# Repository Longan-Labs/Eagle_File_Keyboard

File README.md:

More details please goto [Longan Labs](https://longan-labs.cc/)

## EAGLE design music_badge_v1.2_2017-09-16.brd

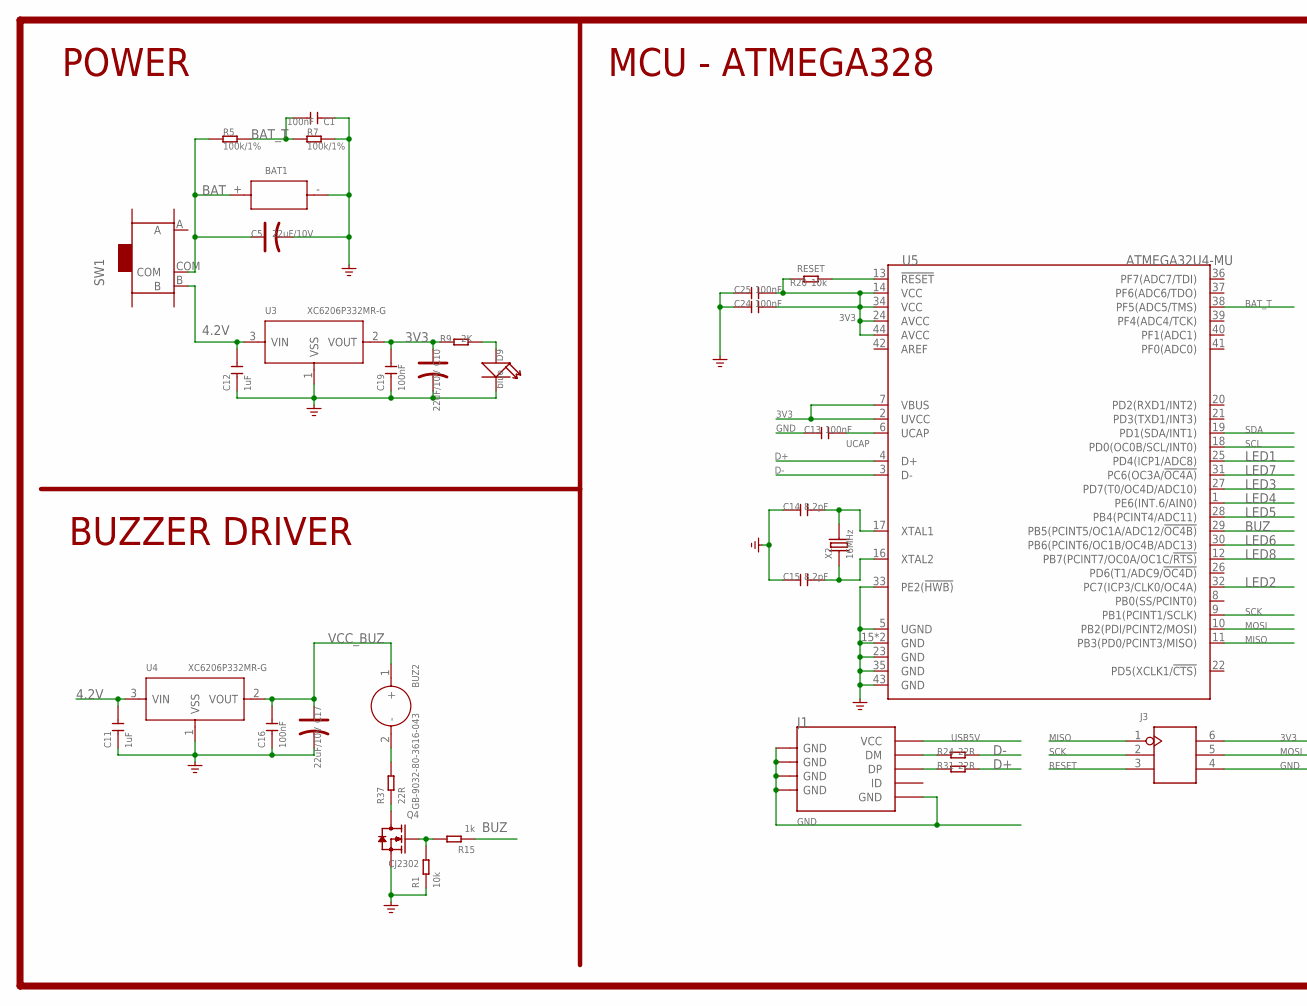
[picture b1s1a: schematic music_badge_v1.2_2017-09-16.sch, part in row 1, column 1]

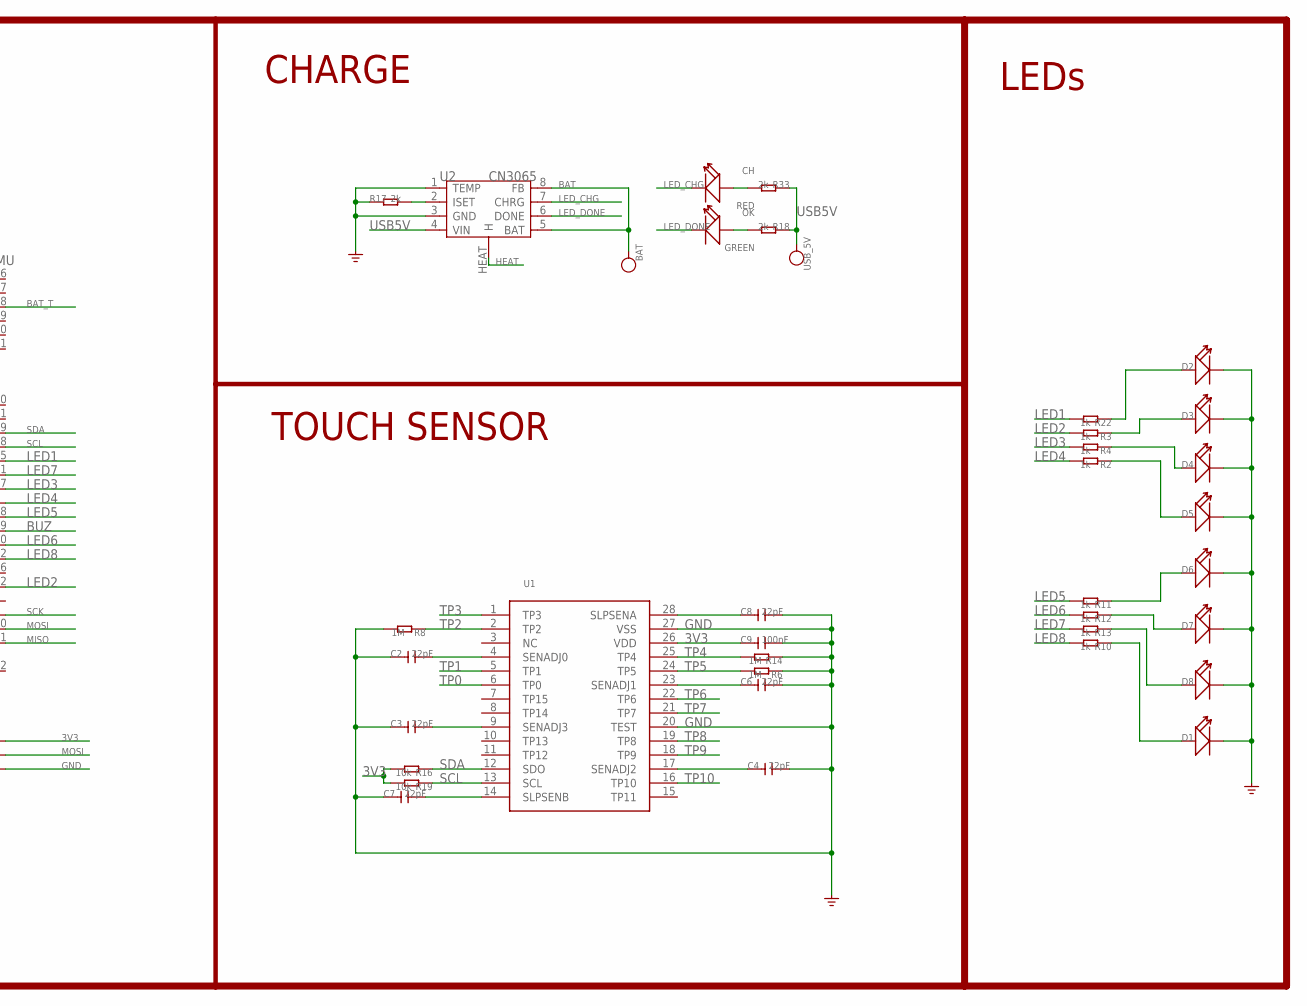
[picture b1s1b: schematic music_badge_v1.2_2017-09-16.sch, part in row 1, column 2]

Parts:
BAT: TEST-POINT-35; TP_3535
BAT1: HOLDER-BATTERY; 2P-SMD-L28.5*W16*H5.5
BUZ2: GB-9032-80-3616-043; BZ2-SMD-9X10.6X3.2MM
C1, C9, C13, C16, C19, C24, C25: 100nF; C0603
C2, C3, C4, C6, C7, C8: 22pF; C0603
C5, C10, C17: 22uF/10V; AVX-B
C11, C12: 1uF; C0603
C14, C15: 8.2pF; C0603
CH: RED; LED-0603
D1, D2, D3, D4, D5, D6, D7, D8: LED-3MM; LED-2P-2.54-3MM
D9: blue; LED-0603@1
J1: USB-MINIUSB-5P-MICRO; MICRO-USB
J3: HEADER-2X3P-2.0-1.143; H2X3-SMD-2.0(1.143)
OK: GREEN; LED-0603
Q4: CJ2302; SOT-23
R1, R16, R19, R20: 10k; R0603
R2, R3, R4, R10, R11, R12, R13, R15, R22: 1k; R0603
R5, R7: 100k/1%; R0603
R6, R8, R14: 1M; R0603
R9: 2K; R0603
R17, R18, R33: 2k; R0603
R24, R31, R37: 22R; R0603
SW1: SWITCH-3P-SMD-6.6X2.8; 3P-SMD-2CH-6.6X2.8-REINFORCE
U1: TTP229-BSF; SSOP28-0.635-10X4MM
U2: CN3065; DFN8
U3, U4: XC6206P332MR-G; SOT-23
U5: ATMEGA32U4-MU; QFN44
USB_5V: TEST-POINT-35; TP_3535
X2: 16MHz; 2P-SMD-5X3.2

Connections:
3V3: C9.1, C10.+, C19.2, C24.2, C25.2, J3.6, R9.1, R16.2, R19.2, R20.1, U1.26 (VDD), U3.2 (VOUT), U5.2 (UVCC), U5.7 (VBUS), U5.14 (VCC), U5.24 (AVCC), U5.34 (VCC), U5.44 (AVCC)
4.2V: C11.2, C12.2, SW1.B, U3.3 (VIN), U4.3 (VIN)
BAT: BAT.T, BAT1.+ (1), C5.+, R5.1, SW1.COM, U2.5 (BAT), U2.8 (FB)
BAT_T: C1.2, R5.2, R7.1, U5.38 (PF5(ADC5/TMS))
BUZ: R15.1, U5.29 (PB5(PCINT5/OC1A/ADC12/!OC4B))
D+: R31.2, U5.4 (D+)
D-: R24.2, U5.3 (D-)
GND: BAT1.- (2), C1.1, C2.1, C3.1, C4.2, C5.-, C6.2, C7.1, C8.2, C9.2, C10.-, C11.1, C12.1, C13.1, C14.1, C15.1, C16.1, C17.-, C19.1, C24.1, C25.1, D1.K (-), D2.K (-), D3.K (-), D4.K (-), D5.K (-), D6.K (-), D7.K (-), D8.K (-), D9.-, J1.5 (GND), J1.S1 (GND), J1.S2 (GND), J1.S3 (GND), J1.S4 (GND), J1.S5 (GND), J1.S6 (GND), J3.4, Q4.2 (S), R1.1, R6.1, R7.2, R8.2, R14.1, R17.1, U1.20 (TEST), U1.27 (VSS), U2.1 (TEMP), U2.3 (GND), U3.1 (VSS), U4.1 (VSS), U5.5 (UGND), U5.15 (GND), U5.23 (GND), U5.33 (PE2(!HWB)), U5.35 (GND), U5.43 (GND), U5.TAB (GND)
HEAT: U2.HEAT (H)
LED1: R22.2, U5.25 (PD4(ICP1/ADC8))
LED2: R3.2, U5.32 (PC7(ICP3/CLK0/OC4A))
LED3: R4.2, U5.27 (PD7(T0/OC4D/ADC10))
LED4: R2.2, U5.1 (PE6(INT.6/AIN0))
LED5: R11.2, U5.28 (PB4(PCINT4/ADC11))
LED6: R12.2, U5.30 (PB6(PCINT6/OC1B/OC4B/ADC13))
LED7: R13.2, U5.31 (PC6(OC3A/!OC4A))
LED8: R10.2, U5.12 (PB7(PCINT7/OC0A/OC1C/!RTS))
LED_CHG: CH.-, U2.7 (CHRG)
LED_DONE: OK.-, U2.6 (DONE)
MISO: J3.1, U5.11 (PB3(PD0/PCINT3/MISO))
MOSI: J3.5, U5.10 (PB2(PDI/PCINT2/MOSI))
unnamed: C2.2, U1.4 (SENADJ0)
unnamed: C3.2, U1.9 (SENADJ3)
unnamed: D9.+, R9.2
unnamed: C7.2, U1.14 (SLPSENB)
unnamed: C6.1, U1.23 (SENADJ1)
unnamed: C14.2, U5.17 (XTAL1), X2.2
unnamed: R17.2, U2.2 (ISET)
unnamed: C4.1, U1.17 (SENADJ2)
unnamed: C8.1, U1.28 (SLPSENA)
unnamed: OK.+, R18.2
unnamed: BUZ2.2 (-), R37.2
unnamed: C15.2, U5.16 (XTAL2), X2.1
unnamed: CH.+, R33.2
unnamed: D6.A (+), R11.1
unnamed: D2.A (+), R22.1
unnamed: D7.A (+), R12.1
unnamed: D1.A (+), R10.1
unnamed: J1.2 (DM), R24.1
unnamed: Q4.1 (G), R1.2, R15.2
unnamed: D4.A (+), R4.1
unnamed: D3.A (+), R3.1
unnamed: D5.A (+), R2.1
unnamed: D8.A (+), R13.1
unnamed: J1.3 (DP), R31.1
unnamed: Q4.3 (D), R37.1
RESET: J3.3, R20.2, U5.13 (!RESET)
SCK: J3.2, U5.9 (PB1(PCINT1/SCLK))
SCL: R19.1, U1.13 (SCL), U5.18 (PD0(OC0B/SCL/INT0))
SDA: R16.1, U1.12 (SDO), U5.19 (PD1(SDA/INT1))
TP0: U1.6 (TP0)
TP1: U1.5 (TP1)
TP2: R8.1, U1.2 (TP2)
TP3: U1.1 (TP3)
TP4: R14.2, U1.25 (TP4)
TP5: R6.2, U1.24 (TP5)
TP6: U1.22 (TP6)
TP7: U1.21 (TP7)
TP8: U1.19 (TP8)
TP9: U1.18 (TP9)
TP10: U1.16 (TP10)
UCAP: C13.2, U5.6 (UCAP)
USB5V: J1.1 (VCC), R18.1, R33.1, U2.4 (VIN), USB_5V.T
VCC_BUZ: BUZ2.1 (+), C16.2, C17.+, U4.2 (VOUT)

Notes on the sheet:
TOUCH SENSOR
CHARGE
MCU - ATMEGA328
POWER
BUZZER DRIVER
LEDs

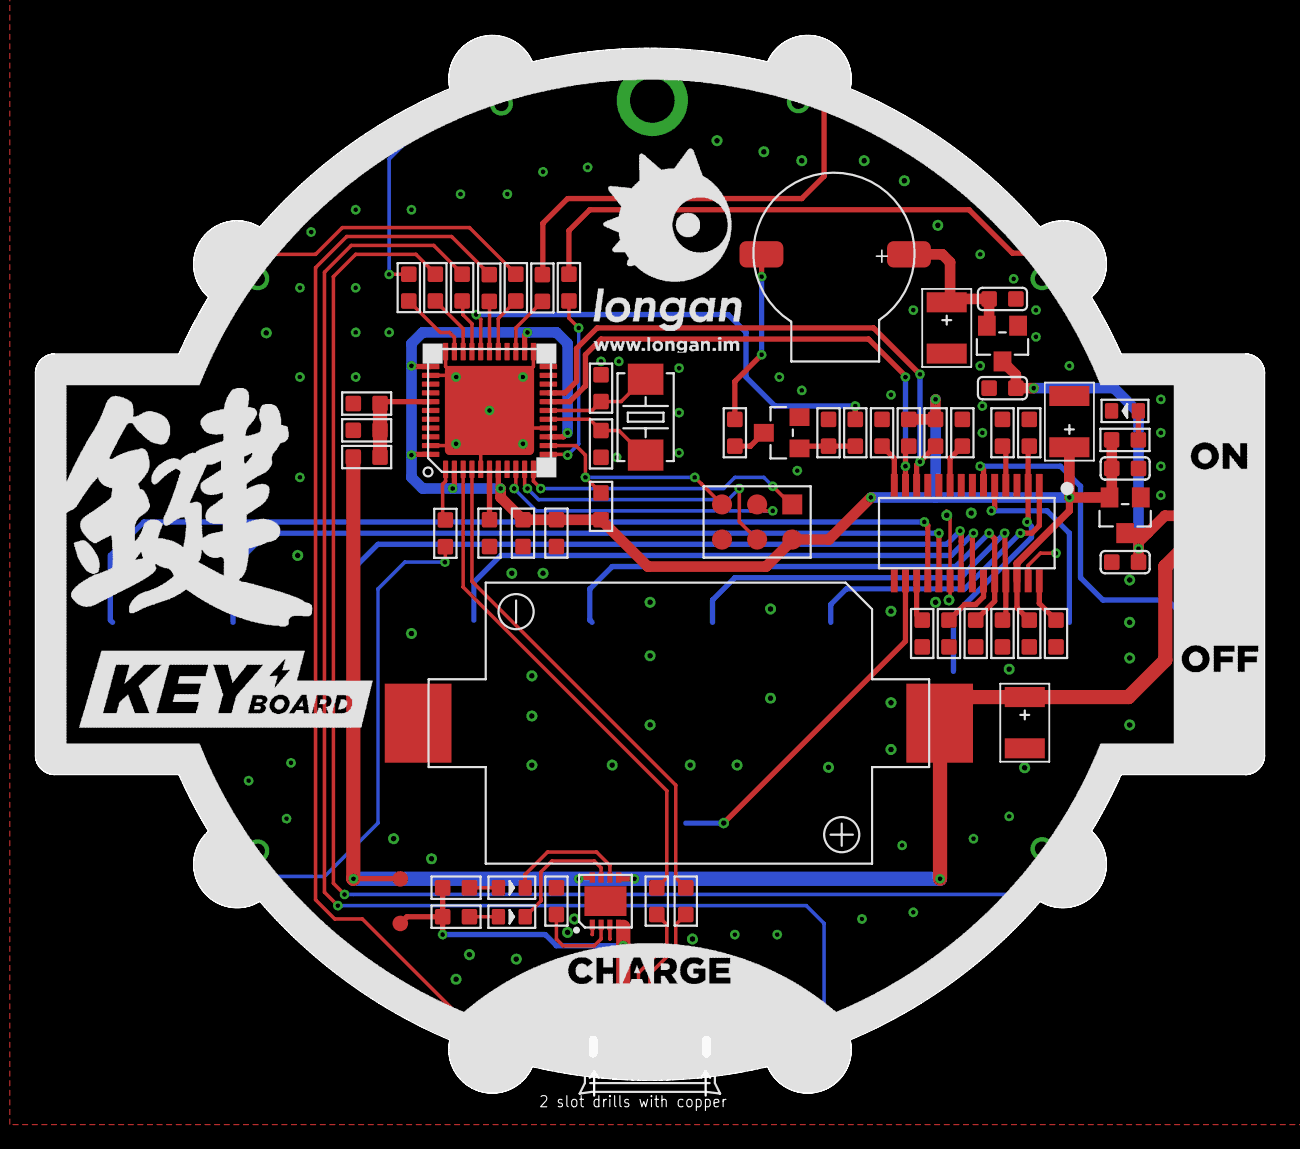
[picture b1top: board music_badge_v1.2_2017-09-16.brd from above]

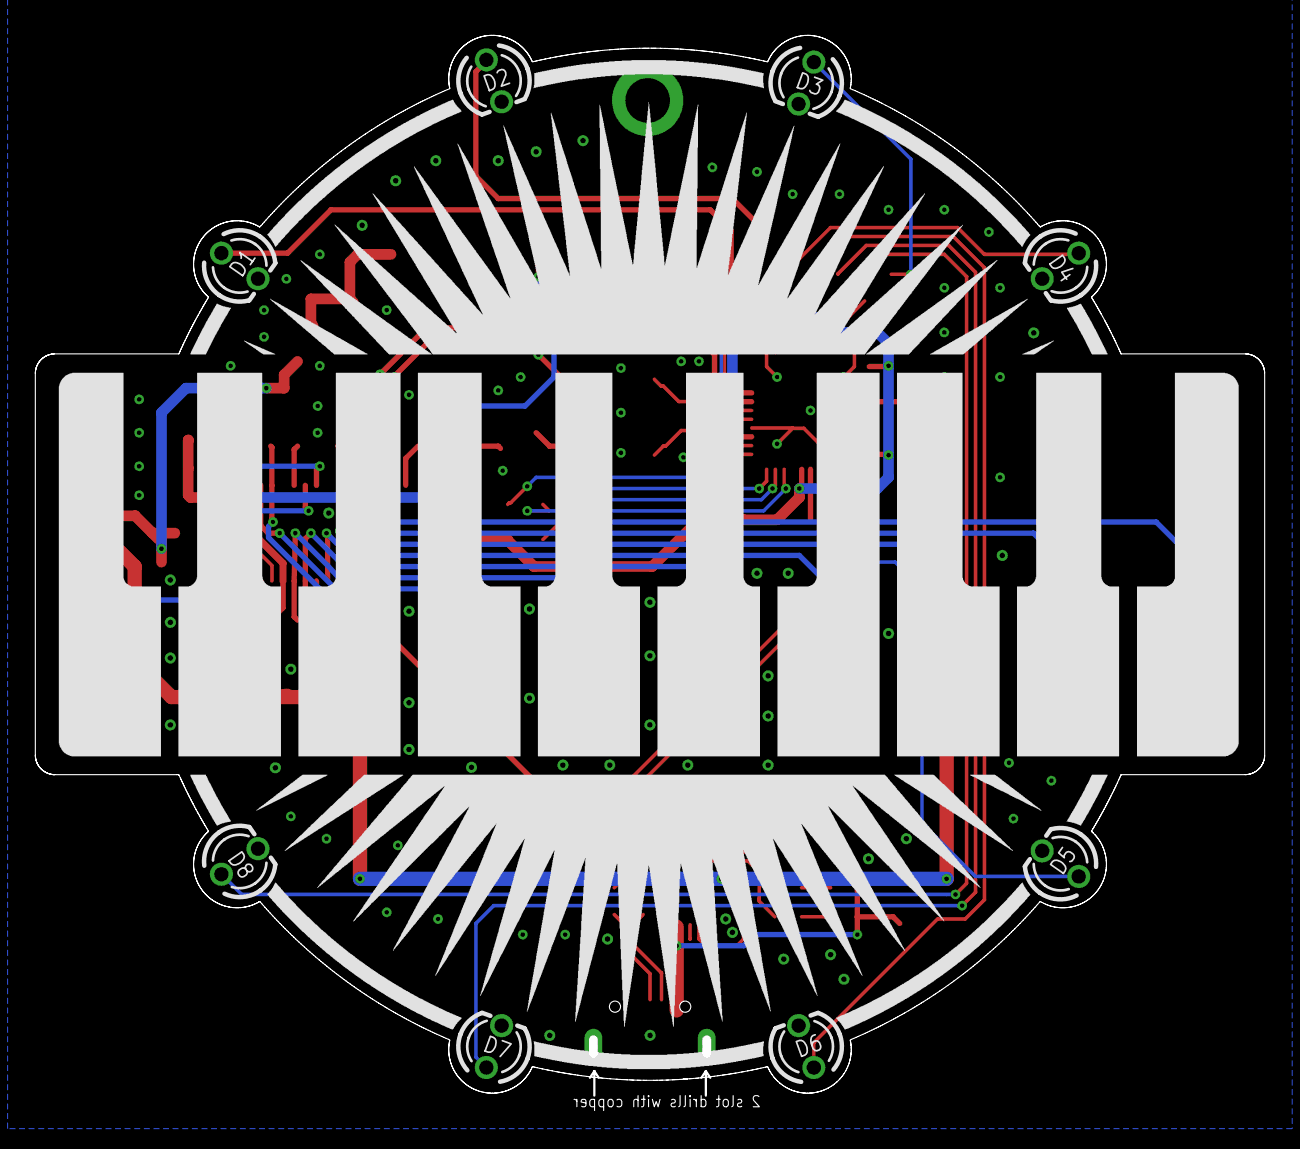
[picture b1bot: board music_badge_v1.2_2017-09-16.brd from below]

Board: 2 copper layers, 69.5 x 60.9 mm, 70 parts (8 on the bottom side), 55 nets.

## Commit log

2018-01-21 first sygn
